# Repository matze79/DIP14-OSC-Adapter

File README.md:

# DIP14 OSC Adapter
7050, 5032, 3225 SMD Oscilator to DIP14 Adapter

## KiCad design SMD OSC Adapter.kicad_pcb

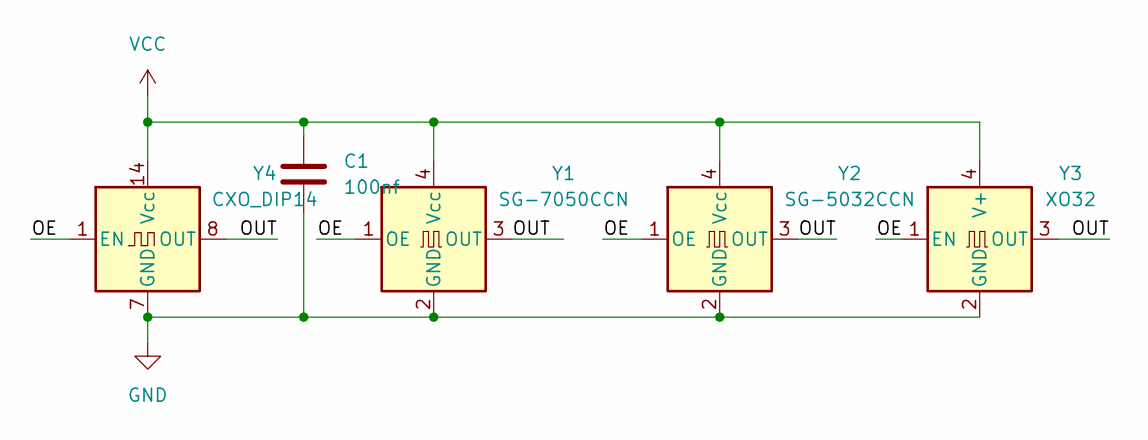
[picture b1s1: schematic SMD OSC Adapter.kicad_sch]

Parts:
C1: 100nf; C_0201_0603Metric_Pad0.64x0.40mm_HandSolder
Y1: SG-7050CCN; Oscillator_SMD_SeikoEpson_SG8002CA-4Pin_7.0x5.0mm
Y2: SG-5032CCN; Oscillator_SMD_SeikoEpson_SG8002LB-4Pin_5.0x3.2mm
Y3: XO32; Oscillator_SMD_EuroQuartz_XO32-4Pin_3.2x2.5mm
Y4: CXO_DIP14; Oscillator_DIP-14

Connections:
/OE: Y1.1 (OE), Y2.1 (OE), Y3.1 (EN), Y4.1 (EN)
/OUT: Y1.3 (OUT), Y2.3 (OUT), Y3.3 (OUT), Y4.8 (OUT)
GND: C1.2, Y1.2 (GND), Y2.2 (GND), Y3.2 (GND), Y4.7 (GND)
VCC: C1.1, Y1.4 (Vcc), Y2.4 (Vcc), Y3.4 (V+), Y4.14 (Vcc)

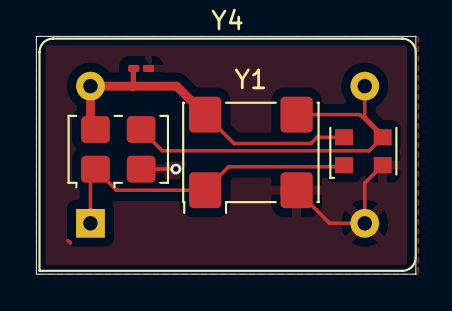
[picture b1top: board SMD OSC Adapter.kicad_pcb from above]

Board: 2 copper layers, 21.1 x 13.2 mm, 5 parts (0 on the bottom side), 4 nets.

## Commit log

2025-11-29 Adapter v01
2025-11-29 Create adapter.png
    PCB Image
2025-11-29 Fix image link in README.md
